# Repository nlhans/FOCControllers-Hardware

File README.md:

# FOCControllers
Exploring the world of FOC with BLDC/Steppers for custom haptic/force feedback in game controllers

Design is WIP.

## MCU
After some exploration, I've chosen to base this design around the STM32H725. There were several close runner ups, including some STM32G4 and F7 parts, and most honourable mention the RP2350. However, the RP2350 was not available from Mouser etc. at the time I started CAD. 
The secondary reason for the STM32H725 is that I still have a handful of these chips unassigned to a project in my parts bin. Considering they weren't cheap while coming in the "large brick" LQFP-176 package, this seemed like a good excuse to finally use them (-: 

Joking aside, this part is quite well suited for experiments with BLDC. Empirical observations using a Nucleo-H743 and the Arduino SimpleFOC library showed that the loopFOC() and move() functions take approximately 3.8 - 4.0us to execute on this chip (approx 1900 CPU cycles). This does not include sensor I/O. That means that running the FOC loop at 5-25kHz (depending on the position sensor datarate) will use around 2-10\% of CPU time. However, in this design I will be using this chip to drive 3 motors, which could bring up the CPU load to 30\%. 

This CPU time excludes I/O time from I2C/SPI bus transfers, or ADC data retrieval, "actual" FOC with DC current feedback, and more importantly, and force feedback algorithms. I would expect when this is all included that 25kHz loop speed would be quite the challenge.

I have also considered the RP2040, as I've used it for some exploration before concluding this design. However its lack of FPU and Cortex-M0+ could not do FOC loop calculations at more than 1kHz due to widespread floating point usage in SimpleFOC. Perhaps 2kHz was attainable when the slow I2C I/O is offloaded to the second core.. but 2kHz is still not a terrific loop speed. It didn't make sense to go through all that effort.

## Motor Driver
I have chosen to use the DRV8316C BLDC driver from Texas Instruments. This chip can use 6-PWM or 3-PWM mode with ENABLE input. The latter is necessary for SimpleFOC implementation of PWM and truth table to the (half-)H bridge drivers. Previous experiments with cheap DRV8833 boards were able to drive a BLDC motor, however, it was not controlling the DRV8833s properly due to its truth table orientated at brushed motor control (long story..). 

Moreover, the DRV8316C chip can operate with 24V supply. and drive 3-5A into motors. I plan to use this magnitude of power for developing an active pedal for simrig racing. These typically require motors in the order of 60-90Watt peak. 

The whole board will be fused for a continuous current of 5A. This may seem awkward to divide across 3 channels, but I expect the duty cycle and concurrent power output to be quite low for this application.

##  Sensing
The board contains, per motor channel, the interfaces for the following sensors:

- I2C magnetic encoders (e.g. As5600)
- SPI or Infineon SSC magnetic encoders (e.g. TLE5012B or TLI5012B)
- Lineair Potentiometer
- NTC for motor temperature
- Current Sense for all 3 coil outputs

The analog sensor channels are connected to a dedicated ADC on the STM32H7 each. The chip will be programmed to convert all channels on each FOC cycle.

All analog channels are referenced against a 3.0V voltage reference. BLDC channel 1 contains a 3.0V regulator to power the analog electronics for all 3 motor channels.

## Other stuff
The PCB contains several support functions which should aid for a configurable & robust driver:

- I2C 24AAxx EEPROM (bitbanged)
- I2C temperature sensor near driver of channel 2 (bitbanged)
- Voltage/Current monitor of input supply
- 5V/Vin 4-pin PWM fan with tacho readout. The board has a 80x80mm form factor in case it runs hot.
- Power clamp to dump regen power (if necessary).
- SPI interface for driving a small LCD
- I2C Grove Connector (hardware I2C)
- 2 UARTs
- 4 Debug LEDs
- 2 Push Buttons
- SWD debug

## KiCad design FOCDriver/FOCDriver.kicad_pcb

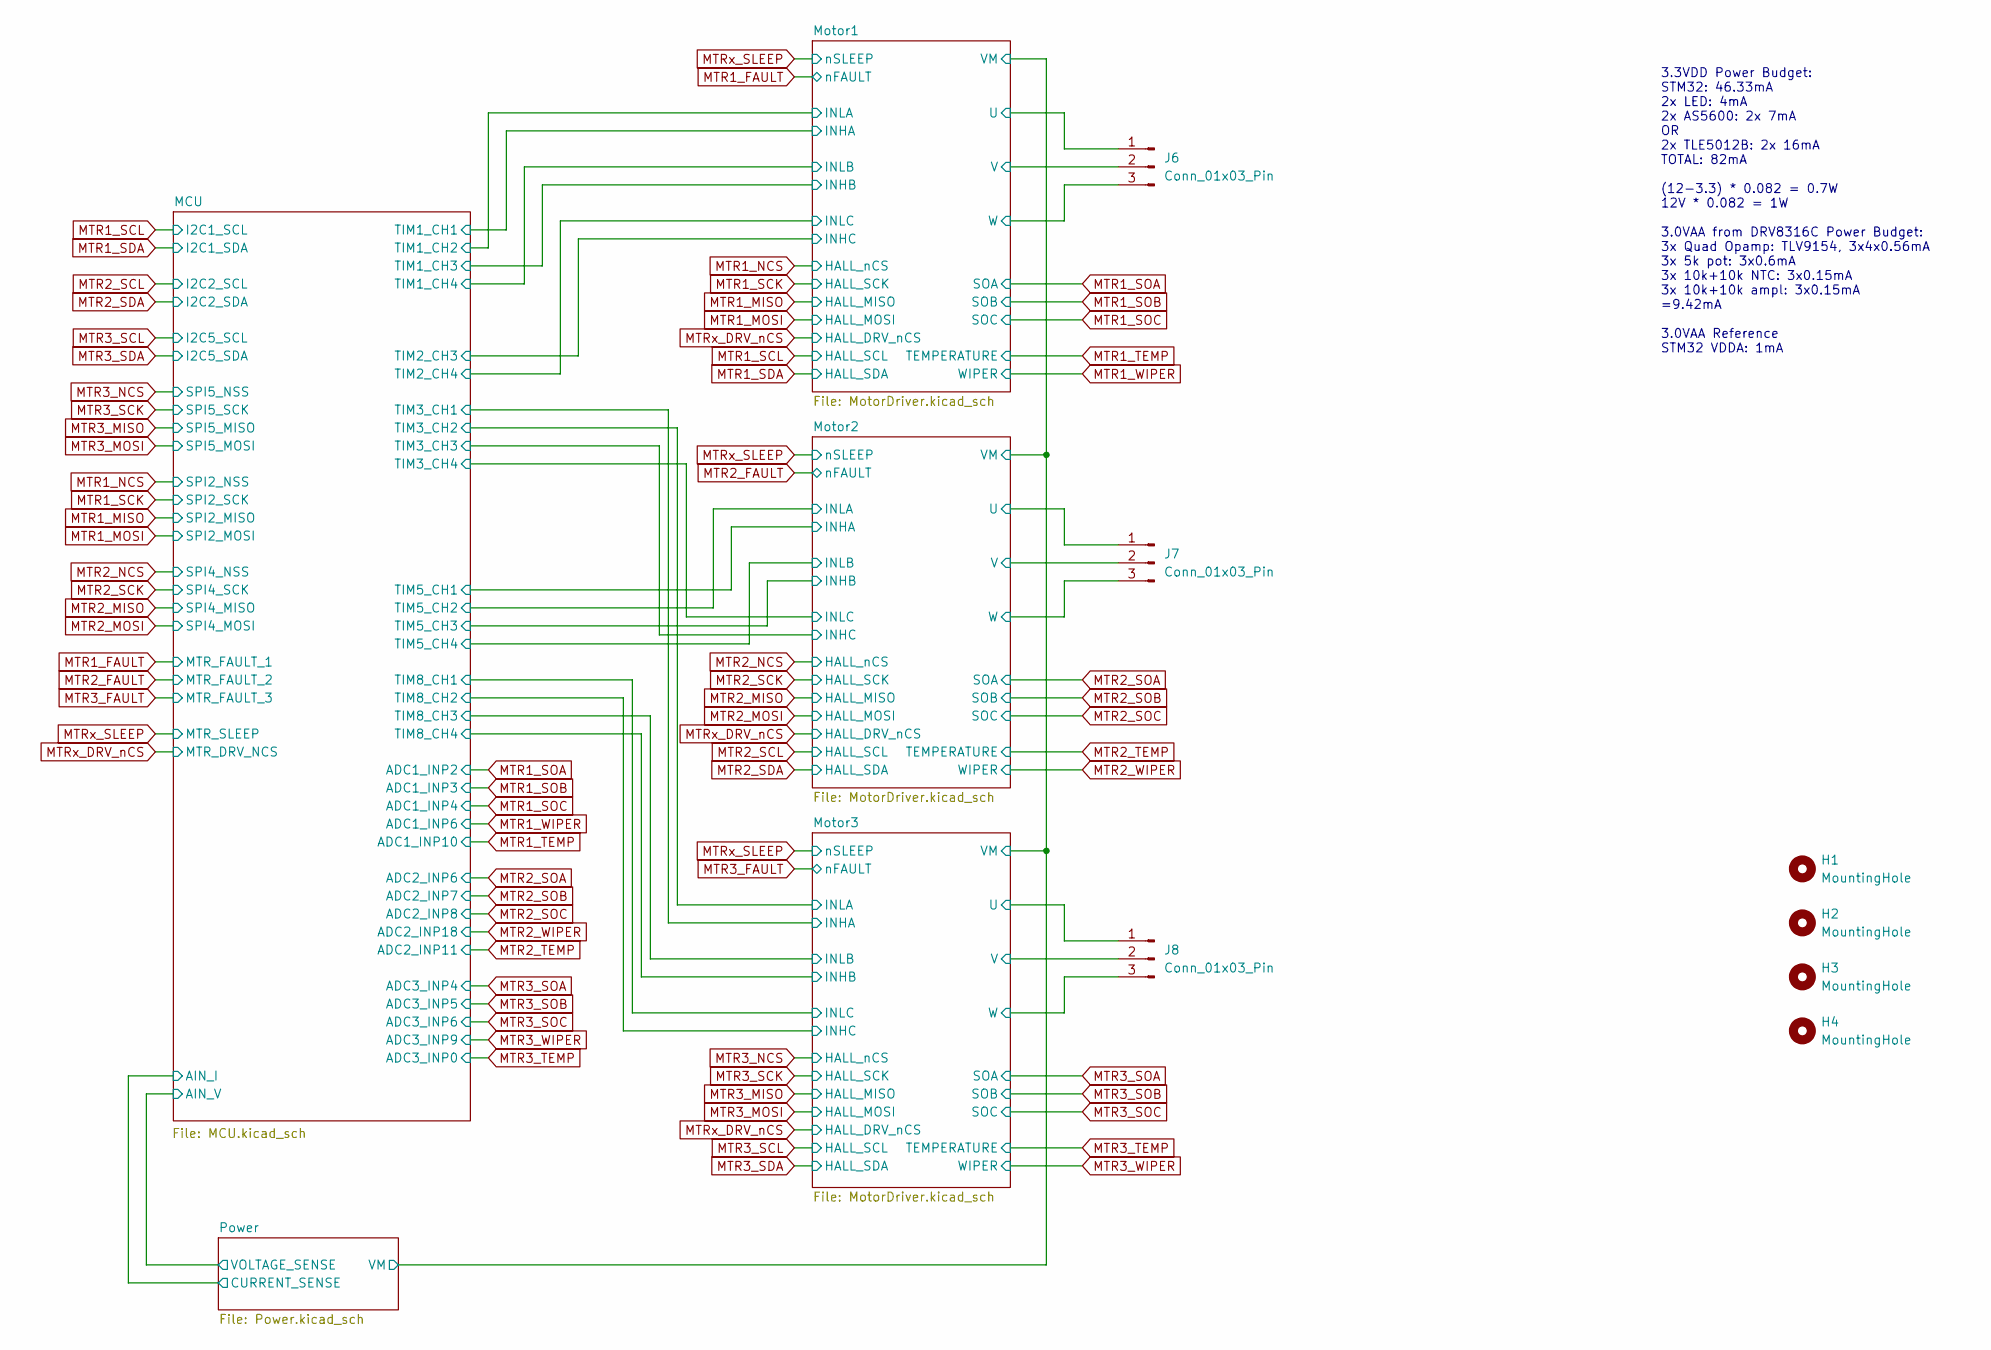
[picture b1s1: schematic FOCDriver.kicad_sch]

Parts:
H1, H2, H3, H4: MountingHole; MountingHole_3.2mm_M3
J6, J7, J8: Conn_01x03_Pin; PinSocket_1x03_P2.54mm_Vertical

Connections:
/Motor1/U: J6.1; also elsewhere on the board
/Motor1/V: J6.2; also elsewhere on the board
/Motor1/W: J6.3; also elsewhere on the board
/Motor2/U: J7.1; also elsewhere on the board
/Motor2/V: J7.2; also elsewhere on the board
/Motor2/W: J7.3; also elsewhere on the board
/Motor3/U: J8.1; also elsewhere on the board
/Motor3/V: J8.2; also elsewhere on the board
/Motor3/W: J8.3; also elsewhere on the board

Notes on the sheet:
3.3VDD Power Budget: STM32: 46.33mA 2x LED: 4mA 2x AS5600: 2x 7mA OR 2x TLE5012B: 2x 16mA TOTAL: 82mA (12-3.3) * 0.082 = 0.7W 12V * 0.082 = 1W 3.0VAA from DRV8316C Power Budget: 3x Quad Opamp: TLV9154, 3x4x0.56mA 3x 5k pot: 3x0.6mA 3x 10k+10k NTC: 3x0.15mA 3x 10k+10k ampl: 3x0.15mA =9.42mA 3.0VAA R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

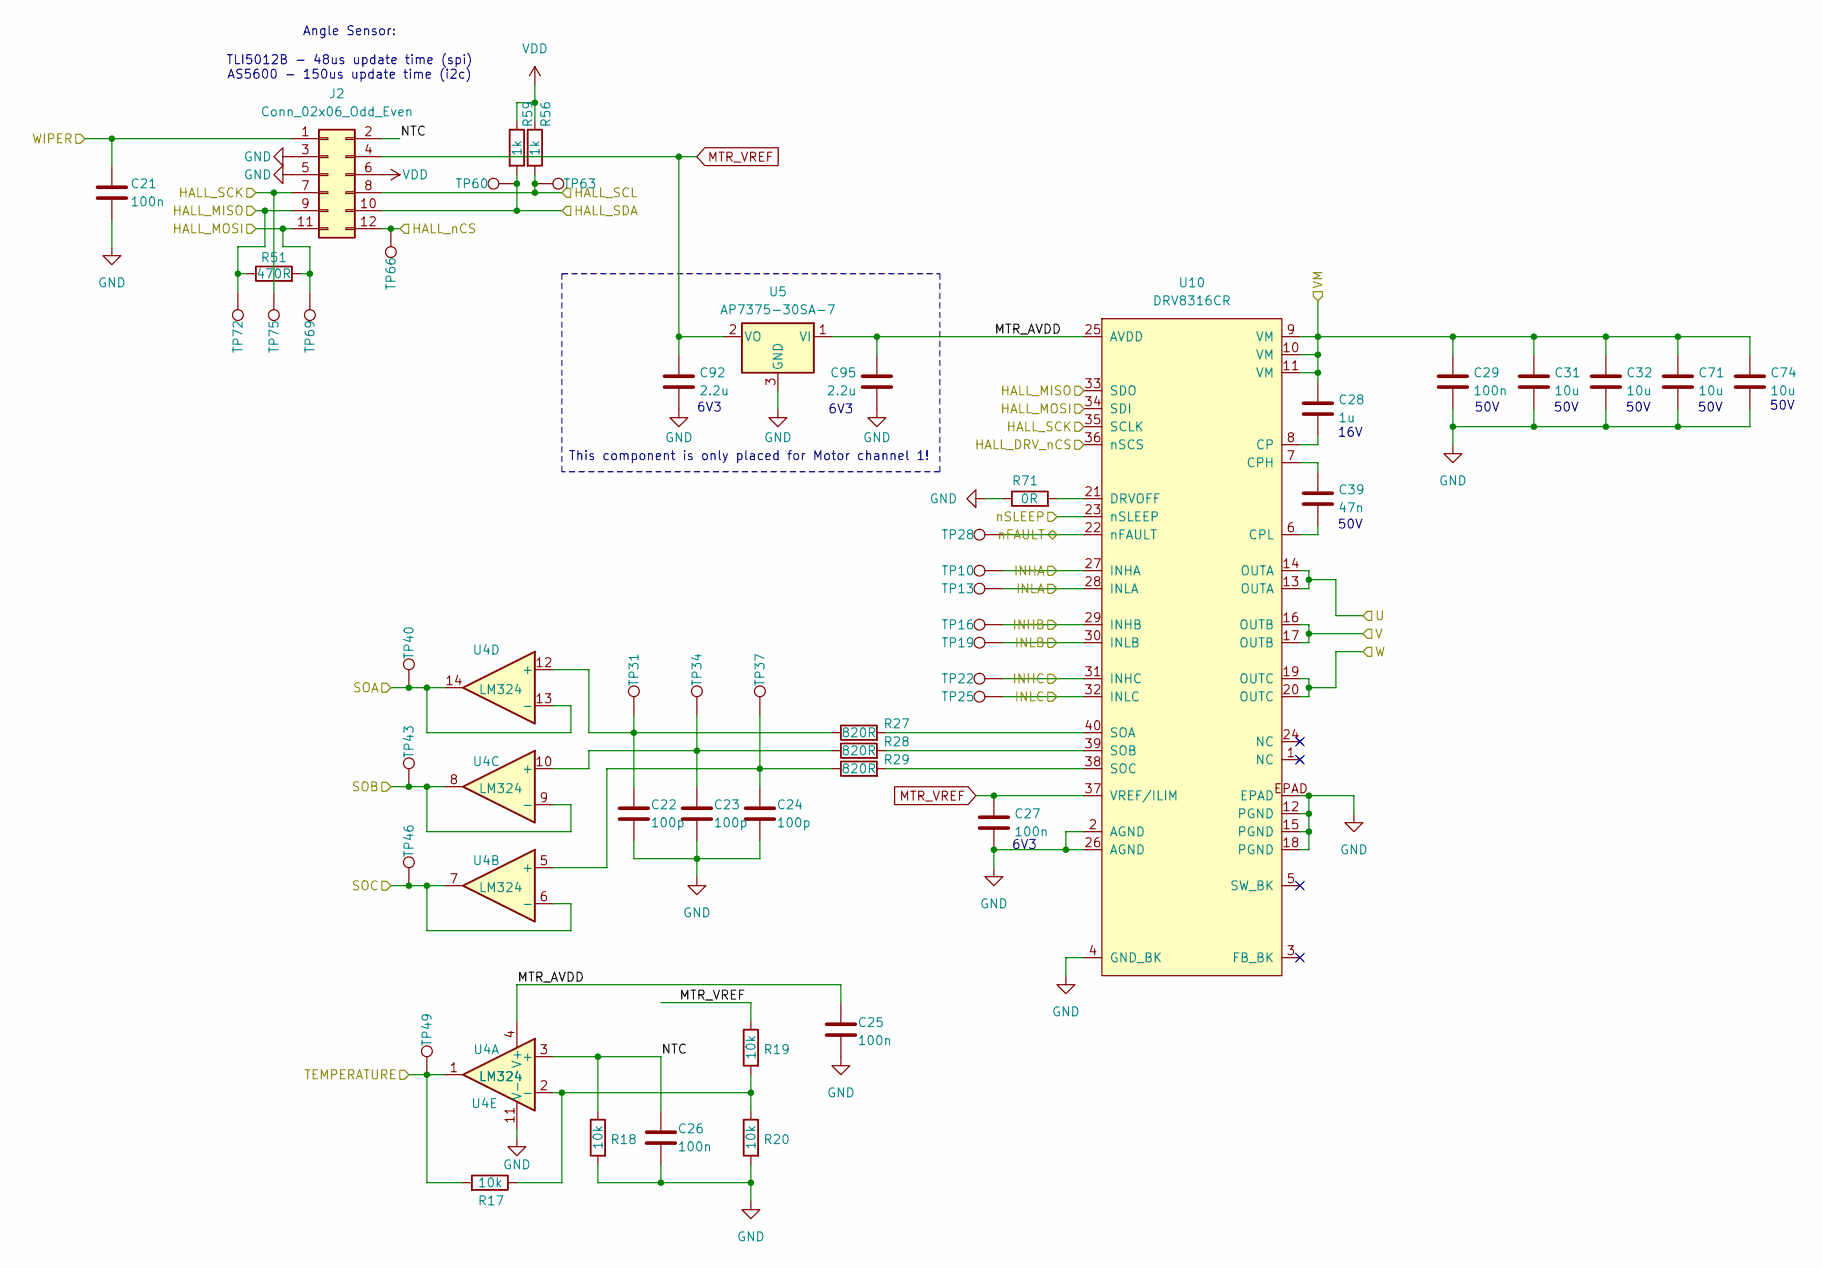
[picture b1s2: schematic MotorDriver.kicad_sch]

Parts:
C21, C25, C26, C27: 100n; Nice_0402C
C22, C23, C24: 100p; Nice_0402C
C28: 1u; Nice_0603C
C29: 100n; Nice_0603C
C31, C32, C71, C74: 10u; C_1206_3216Metric
C39: 47n; Nice_0603C
C92, C95: 2.2u; Nice_0603C
J2: Conn_02x06_Odd_Even; PinSocket_2x06_P2.54mm_Horizontal
R17, R18, R19, R20: 10k; Nice_0402R
R27, R28, R29: 820R; Nice_0402R
R51: 470R; Nice_0402R
R56, R59: 1k; Nice_0402R
R71: 0R; Nice_0402R
TP10, TP13, TP16, TP19, TP22, TP25, TP28, TP31, TP34, TP37, TP40, TP43, TP46, TP49, TP60, TP63, TP66, TP69, TP72, TP75: TestPoint; TP_0.6mm
U4: LM324; TSSOP-14_4.4x5mm_P0.65mm
U5: AP7375-30SA-7; SOT-23; MPN AP7375-30SA-7
U10: DRV8316CR; VQFN40_RGF_TEX; MPN DRV8316CRRGFR

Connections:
/MCU/TIM1_CH1: TP10.1, U10.27 (INHA); also elsewhere on the board
/MCU/TIM1_CH2: TP13.1, U10.28 (INLA); also elsewhere on the board
/MCU/TIM1_CH3: TP16.1, U10.29 (INHB); also elsewhere on the board
/MCU/TIM1_CH4: TP19.1, U10.30 (INLB); also elsewhere on the board
/MCU/TIM2_CH3: TP22.1, U10.31 (INHC); also elsewhere on the board
/MCU/TIM2_CH4: TP25.1, U10.32 (INLC); also elsewhere on the board
/Motor1/MTR_AVDD: C25.1, C95.1, U4.4 (V+), U5.1 (VI), U10.25 (AVDD)
/Motor1/NTC: C26.1, J2.2, R18.1, U4.3 (+)
/Motor1/U: U10.13 (OUTA), U10.14 (OUTA); also elsewhere on the board
/Motor1/V: U10.16 (OUTB), U10.17 (OUTB); also elsewhere on the board
/Motor1/VM: C28.1, C29.1, C31.1, C32.1, C71.1, C74.1, U10.9 (VM), U10.10 (VM), U10.11 (VM); also elsewhere on the board
/Motor1/W: U10.19 (OUTC), U10.20 (OUTC); also elsewhere on the board
GND: C21.2, C22.2, C23.2, C24.2, C25.2, C26.2, C27.2, C29.2, C31.2, C32.2, C71.2, C74.2, C92.2, C95.2, J2.3, J2.5, R18.2, R20.2, R71.1, U4.11 (V-), U5.3 (GND), U10.2 (AGND), U10.4 (GND_BK), U10.12 (PGND), U10.15 (PGND), U10.18 (PGND), U10.26 (AGND), U10.EPAD; also elsewhere on the board
MTR1_FAULT: TP28.1, U10.22 (nFAULT); also elsewhere on the board
MTR1_MISO: J2.9, R51.1, TP72.1, U10.33 (SDO); also elsewhere on the board
MTR1_MOSI: J2.11, R51.2, TP69.1, U10.34 (SDI); also elsewhere on the board
MTR1_NCS: J2.12, TP66.1; also elsewhere on the board
MTR1_SCK: J2.7, TP75.1, U10.35 (SCLK); also elsewhere on the board
MTR1_SCL: J2.8, R56.2, TP63.1; also elsewhere on the board
MTR1_SDA: J2.10, R59.2, TP60.1; also elsewhere on the board
MTR1_SOA: TP40.1, U4.13 (-), U4.14; also elsewhere on the board
MTR1_SOB: TP43.1, U4.8, U4.9 (-); also elsewhere on the board
MTR1_SOC: TP46.1, U4.6 (-), U4.7; also elsewhere on the board
MTR1_TEMP: R17.2, TP49.1, U4.1; also elsewhere on the board
MTR1_WIPER: C21.1, J2.1; also elsewhere on the board
MTR_VREF: C27.1, C92.1, J2.4, R19.1, U5.2 (VO), U10.37 (VREF/ILIM); also elsewhere on the board
MTRx_DRV_nCS: U10.36 (nSCS); also elsewhere on the board
MTRx_SLEEP: U10.23 (nSLEEP); also elsewhere on the board
unnamed: R17.1, R19.2, R20.1, U4.2 (-)
unnamed: C24.1, R29.1, TP37.1, U4.5 (+)
unnamed: C23.1, R28.1, TP34.1, U4.10 (+)
unnamed: C22.1, R27.1, TP31.1, U4.12 (+)
unnamed: C28.2, U10.8 (CP)
unnamed: C39.1, U10.7 (CPH)
unnamed: C39.2, U10.6 (CPL)
unnamed: R71.2, U10.21 (DRVOFF)
unnamed: R27.2, U10.40 (SOA)
unnamed: R28.2, U10.39 (SOB)
unnamed: R29.2, U10.38 (SOC)
VDD: J2.6, R56.1, R59.1; also elsewhere on the board

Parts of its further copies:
C9, C13, C15, C34, C38, C40, C88, C89: 100n; Nice_0402C
C10, C11, C12, C35, C36, C37: 100p; Nice_0402C
C16, C41: 1u; Nice_0603C
C17, C42: 100n; Nice_0603C
C19, C20, C44, C45, C72, C73, C75, C76: 10u; C_1206_3216Metric
C48, C87: 47n; Nice_0603C
C96, C97: 2.2u; Nice_0603C
J1, J3: Conn_02x06_Odd_Even; PinSocket_2x06_P2.54mm_Horizontal
R4, R5, R6, R7, R33, R34, R35, R36: 10k; Nice_0402R
R14, R15, R16, R43, R44, R45: 820R; Nice_0402R
R52, R65: 470R; Nice_0402R
R57, R58, R60, R61: 1k; Nice_0402R
R72, R73: 0R; Nice_0402R
TP11, TP12, TP14, TP15, TP17, TP18, TP20, TP21, TP23, TP24, TP26, TP27, TP29, TP30, TP32, TP33, TP35, TP36, TP38, TP39, TP41, TP42, TP44, TP45, TP47, TP48, TP50, TP51, TP61, TP62, TP64, TP65, TP67, TP68, TP70, TP71, TP73, TP74, TP76, TP77: TestPoint; TP_0.6mm
U2, U7: LM324; TSSOP-14_4.4x5mm_P0.65mm
U15, U16: DRV8316CR; VQFN40_RGF_TEX; MPN DRV8316CRRGFR

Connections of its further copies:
/MCU/TIM3_CH1: TP12.1, U16.27 (INHA); also elsewhere on the board
/MCU/TIM3_CH2: TP15.1, U16.28 (INLA); also elsewhere on the board
/MCU/TIM3_CH3: TP23.1, U15.31 (INHC); also elsewhere on the board
/MCU/TIM3_CH4: TP26.1, U15.32 (INLC); also elsewhere on the board
/MCU/TIM5_CH1: TP11.1, U15.27 (INHA); also elsewhere on the board
/MCU/TIM5_CH2: TP14.1, U15.28 (INLA); also elsewhere on the board
/MCU/TIM5_CH3: TP17.1, U15.29 (INHB); also elsewhere on the board
/MCU/TIM5_CH4: TP20.1, U15.30 (INLB); also elsewhere on the board
/MCU/TIM8_CH1: TP27.1, U16.32 (INLC); also elsewhere on the board
/MCU/TIM8_CH2: TP24.1, U16.31 (INHC); also elsewhere on the board
/MCU/TIM8_CH3: TP21.1, U16.30 (INLB); also elsewhere on the board
/MCU/TIM8_CH4: TP18.1, U16.29 (INHB); also elsewhere on the board
/Motor1/VM: C16.1, C17.1, C19.1, C20.1, C41.1, C42.1, C44.1, C45.1, C72.1, C73.1, C75.1, C76.1, U15.9 (VM), U15.10 (VM), U15.11 (VM), U16.9 (VM), U16.10 (VM), U16.11 (VM); also elsewhere on the board
/Motor2/MTR_AVDD: C13.1, C96.1, U2.4 (V+), U15.25 (AVDD)
/Motor2/NTC: C88.1, J1.2, R5.1, U2.3 (+)
/Motor2/U: U15.13 (OUTA), U15.14 (OUTA); also elsewhere on the board
/Motor2/V: U15.16 (OUTB), U15.17 (OUTB); also elsewhere on the board
/Motor2/W: U15.19 (OUTC), U15.20 (OUTC); also elsewhere on the board
/Motor3/MTR_AVDD: C38.1, C97.1, U7.4 (V+), U16.25 (AVDD)
/Motor3/NTC: C89.1, J3.2, R34.1, U7.3 (+)
/Motor3/U: U16.13 (OUTA), U16.14 (OUTA); also elsewhere on the board
/Motor3/V: U16.16 (OUTB), U16.17 (OUTB); also elsewhere on the board
/Motor3/W: U16.19 (OUTC), U16.20 (OUTC); also elsewhere on the board
GND: C9.2, C10.2, C11.2, C12.2, C13.2, C15.2, C17.2, C19.2, C20.2, C34.2, C35.2, C36.2, C37.2, C38.2, C40.2, C42.2, C44.2, C45.2, C72.2, C73.2, C75.2, C76.2, C88.2, C89.2, C96.2, C97.2, J1.3, J1.5, J3.3, J3.5, R5.2, R7.2, R34.2, R36.2, R72.1, R73.1, U2.11 (V-), U7.11 (V-), U15.2 (AGND), U15.4 (GND_BK), U15.12 (PGND), U15.15 (PGND), U15.18 (PGND), U15.26 (AGND), U15.EPAD, U16.2 (AGND), U16.4 (GND_BK), U16.12 (PGND), U16.15 (PGND), U16.18 (PGND), U16.26 (AGND), U16.EPAD; also elsewhere on the board
MTR2_FAULT: TP29.1, U15.22 (nFAULT); also elsewhere on the board
MTR2_MISO: J1.9, R52.1, TP73.1, U15.33 (SDO); also elsewhere on the board
MTR2_MOSI: J1.11, R52.2, TP70.1, U15.34 (SDI); also elsewhere on the board
MTR2_NCS: J1.12, TP67.1; also elsewhere on the board
MTR2_SCK: J1.7, TP76.1, U15.35 (SCLK); also elsewhere on the board
MTR2_SCL: J1.8, R57.2, TP64.1; also elsewhere on the board
MTR2_SDA: J1.10, R60.2, TP61.1; also elsewhere on the board
MTR2_SOA: TP41.1, U2.13 (-), U2.14; also elsewhere on the board
MTR2_SOB: TP44.1, U2.8, U2.9 (-); also elsewhere on the board
MTR2_SOC: TP47.1, U2.6 (-), U2.7; also elsewhere on the board
MTR2_TEMP: R4.2, TP50.1, U2.1; also elsewhere on the board
MTR2_WIPER: C9.1, J1.1; also elsewhere on the board
MTR3_FAULT: TP30.1, U16.22 (nFAULT); also elsewhere on the board
MTR3_MISO: J3.9, R65.1, TP74.1, U16.33 (SDO); also elsewhere on the board
MTR3_MOSI: J3.11, R65.2, TP71.1, U16.34 (SDI); also elsewhere on the board
MTR3_NCS: J3.12, TP68.1; also elsewhere on the board
MTR3_SCK: J3.7, TP77.1, U16.35 (SCLK); also elsewhere on the board
MTR3_SCL: J3.8, R58.2, TP65.1; also elsewhere on the board
MTR3_SDA: J3.10, R61.2, TP62.1; also elsewhere on the board
MTR3_SOA: TP42.1, U7.13 (-), U7.14; also elsewhere on the board
MTR3_SOB: TP45.1, U7.8, U7.9 (-); also elsewhere on the board
MTR3_SOC: TP48.1, U7.6 (-), U7.7; also elsewhere on the board
MTR3_TEMP: R33.2, TP51.1, U7.1; also elsewhere on the board
MTR3_WIPER: C34.1, J3.1; also elsewhere on the board
MTR_VREF: C15.1, C40.1, J1.4, J3.4, R6.1, R35.1, U15.37 (VREF/ILIM), U16.37 (VREF/ILIM); also elsewhere on the board
MTRx_DRV_nCS: U15.36 (nSCS), U16.36 (nSCS); also elsewhere on the board
MTRx_SLEEP: U15.23 (nSLEEP), U16.23 (nSLEEP); also elsewhere on the board
unnamed: R4.1, R6.2, R7.1, U2.2 (-)
unnamed: C12.1, R16.1, TP38.1, U2.5 (+)
unnamed: C11.1, R15.1, TP35.1, U2.10 (+)
unnamed: C10.1, R14.1, TP32.1, U2.12 (+)
unnamed: R33.1, R35.2, R36.1, U7.2 (-)
unnamed: C37.1, R45.1, TP39.1, U7.5 (+)
unnamed: C36.1, R44.1, TP36.1, U7.10 (+)
unnamed: C35.1, R43.1, TP33.1, U7.12 (+)
unnamed: C16.2, U15.8 (CP)
unnamed: C48.1, U15.7 (CPH)
unnamed: C48.2, U15.6 (CPL)
unnamed: R72.2, U15.21 (DRVOFF)
unnamed: R14.2, U15.40 (SOA)
unnamed: R15.2, U15.39 (SOB)
unnamed: R16.2, U15.38 (SOC)
unnamed: C41.2, U16.8 (CP)
unnamed: C87.1, U16.7 (CPH)
unnamed: C87.2, U16.6 (CPL)
unnamed: R73.2, U16.21 (DRVOFF)
unnamed: R43.2, U16.40 (SOA)
unnamed: R44.2, U16.39 (SOB)
unnamed: R45.2, U16.38 (SOC)
VDD: J1.6, J3.6, R57.1, R58.1, R60.1, R61.1; also elsewhere on the board

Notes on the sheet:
50V
Angle Sensor: TLI5012B - 48us update time (spi) AS5600 - 150us update time (i2c)
6V3
16V
This component is only placed for Motor channel 1!

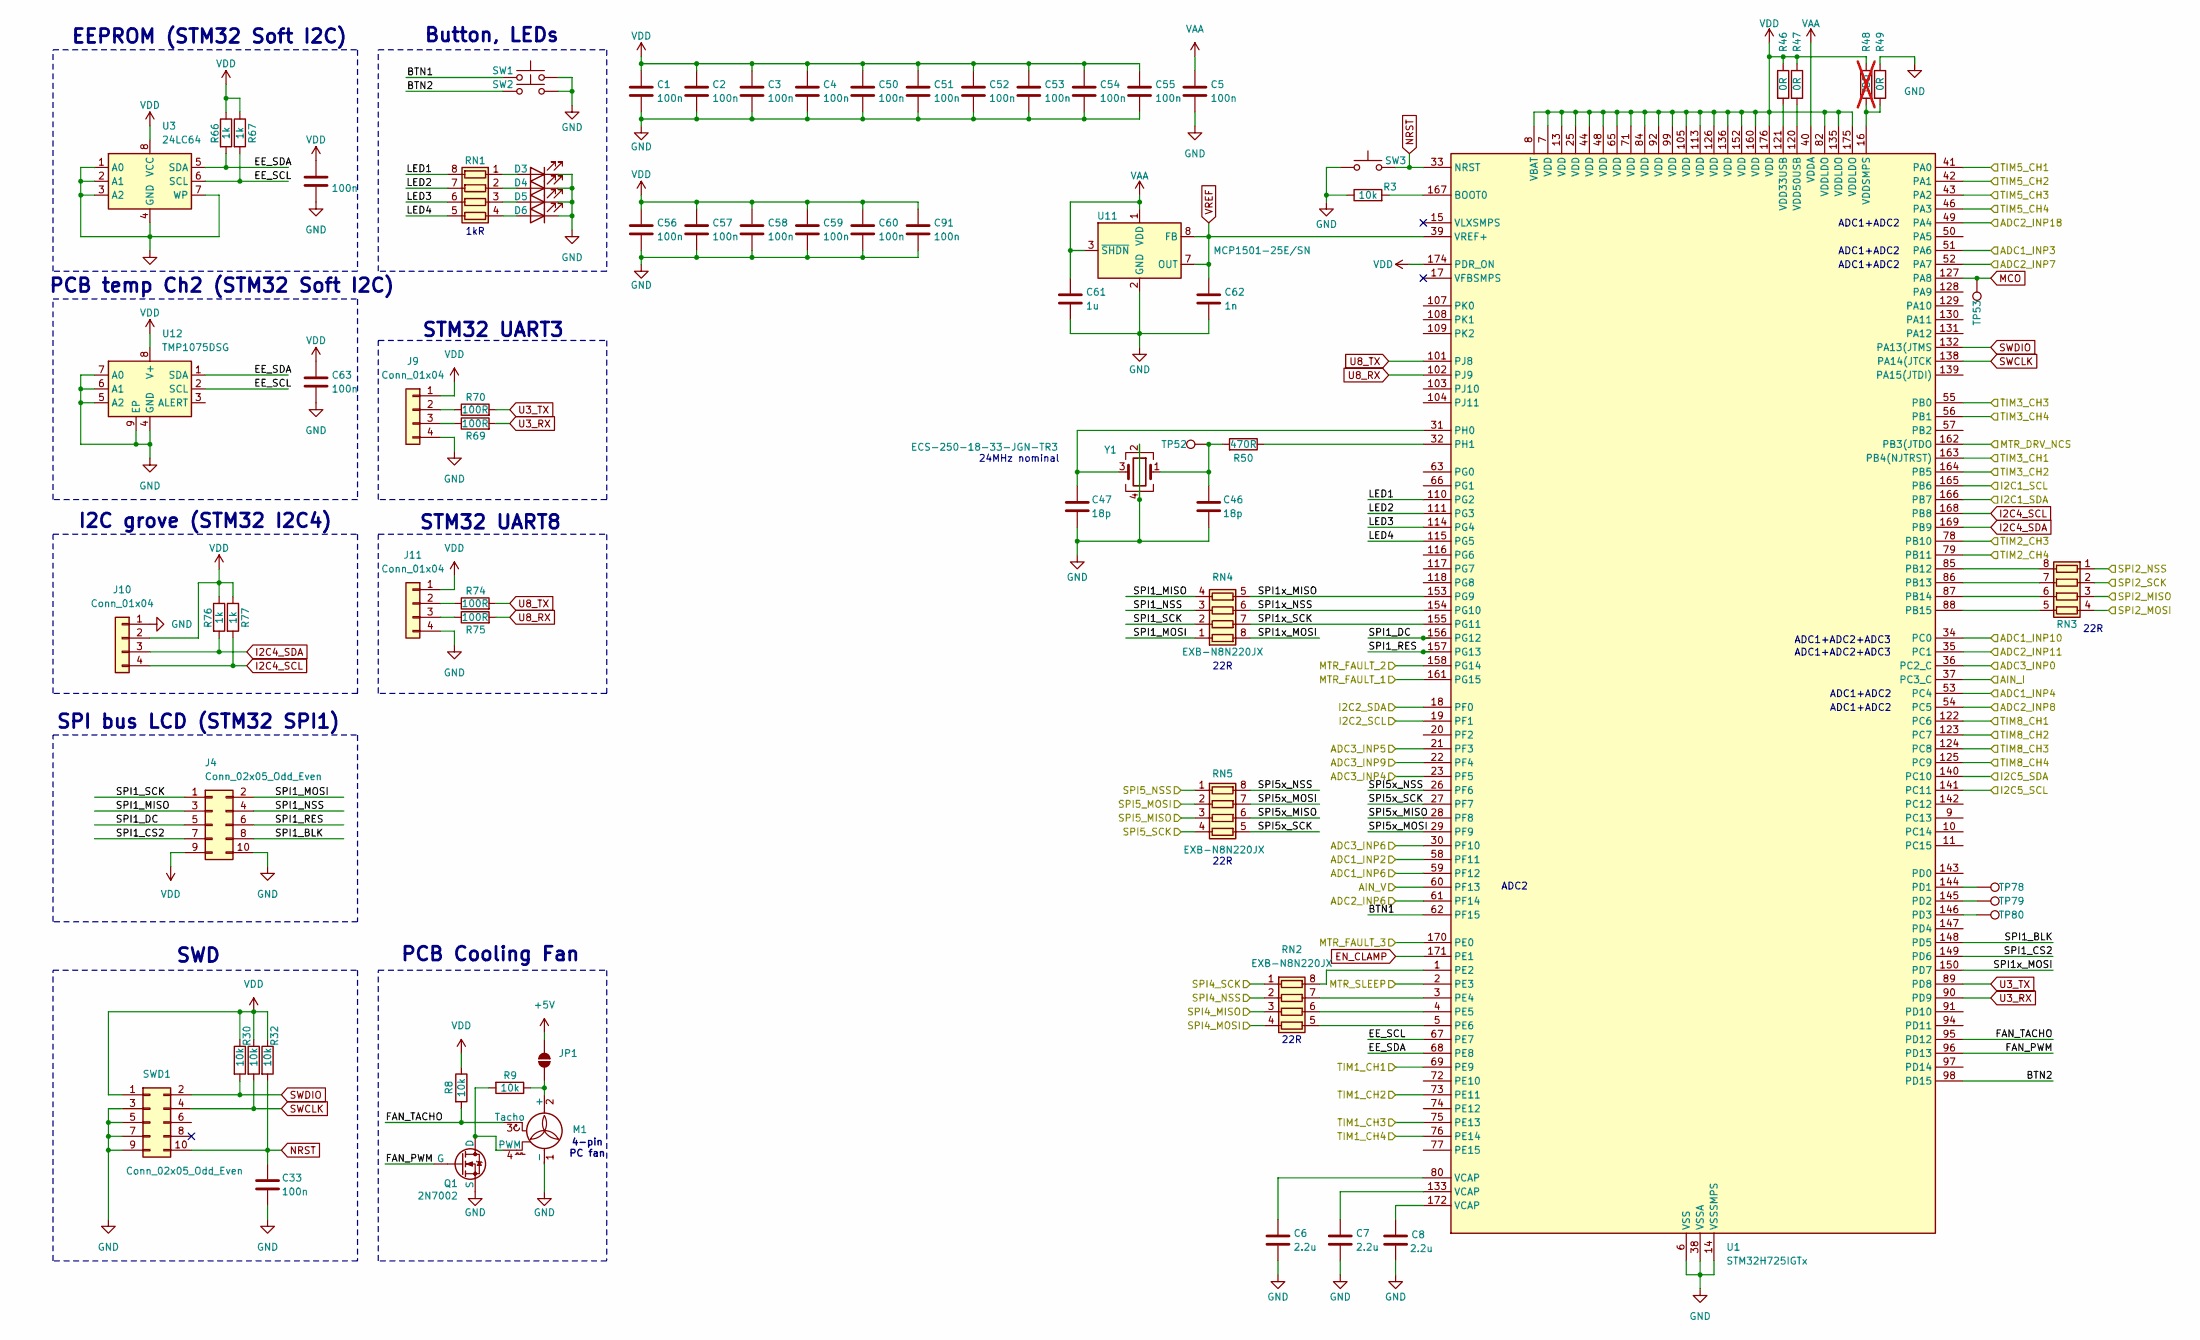
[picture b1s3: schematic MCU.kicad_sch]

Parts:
C1, C2, C3, C4, C5, C33, C49, C50, C51, C52, C53, C54, C55, C56, C57, C58, C59, C60, C63, C91: 100n; Nice_0402C
C6, C7, C8: 2.2u; Nice_0603C
C46, C47: 18p; Nice_0402C
C61: 1u; Nice_0603C
C62: 1n; Nice_0402C
D3, D4, D5, D6: APT2012SYCK; LED_0805_2012Metric; MPN APT2012SYCK
J4: Conn_02x05_Odd_Even; PinHeader_2x05_P2.54mm_Vertical
J9, J11: Conn_01x04; PinHeader_1x04_P2.54mm_Vertical
J10: Conn_01x04; JST_PH_B4B-PH-K_1x04_P2.00mm_Vertical
JP1: SolderJumper_2_Open; SolderJumper-2_P1.3mm_Open_Pad1.0x1.5mm
M1: Fan_Tacho_PWM; FanPinHeader_1x04_P2.54mm_Vertical
Q1: 2N7002; SOT-23
R3, R8, R9, R30, R31, R32: 10k; Nice_0402R
R46, R47, R49: 0R; Nice_0402R
R48: TBD; Nice_0402DNP; not fitted
R50: 470R; Nice_0402R
R66, R67, R76, R77: 1k; Nice_0402R
R69, R70, R74, R75: 100R; Nice_0402R
RN1: EXB-38V102JV; R_Array_Convex_4x0603
RN2, RN3, RN4, RN5: EXB-N8N220JX; R_Array_Concave_4x0402
SW1, SW2, SW3: SW_Push; SW_PUSH_1P1T_6x3.5mm_H5.0_APEM_MJTP1250
SWD1: Conn_02x05_Odd_Even; PinHeader_2x05_P1.27mm_Vertical_SMD
TP52, TP53, TP78, TP79, TP80: TestPoint; TP_0.6mm
U1: STM32H725IGTx; LQFP-176_24x24mm_P0.5mm
U3: 24LC64; SOIC-8_3.9x4.9mm_P1.27mm
U11: MCP1501-25E/SN; SOIC-8_3.9x4.9mm_P1.27mm; MPN MCP1501-25E/SN
U12: TMP1075DSG; WSON-8-1EP_2x2mm_P0.5mm_EP0.9x1.6mm_ThermalVias
Y1: ECS-250-18-33-JGN-TR3; Crystal_SMD_3225-4Pin_3.2x2.5mm; MPN ECS-250-18-33-JGN-TR3

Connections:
+5V: JP1.2 (B); also elsewhere on the board
/MCU/AIN_I: U1.37 (PC3_C); also elsewhere on the board
/MCU/AIN_V: U1.60 (PF13); also elsewhere on the board
/MCU/BTN1: SW1.2, U1.62 (PF15)
/MCU/BTN2: SW2.2, U1.98 (PD15)
/MCU/EE_SCL: R67.2, U1.67 (PE7), U3.6 (SCL), U12.2 (SCL)
/MCU/EE_SDA: R66.2, U1.68 (PE8), U3.5 (SDA), U12.1 (SDA)
/MCU/FAN_PWM: Q1.1 (G), U1.96 (PD13)
/MCU/FAN_TACHO: M1.3 (Tacho), R8.2, U1.95 (PD12)
/MCU/LED1: RN1.8 (R1.2), U1.110 (PG2)
/MCU/LED2: RN1.7 (R2.2), U1.111 (PG3)
/MCU/LED3: RN1.6 (R3.2), U1.114 (PG4)
/MCU/LED4: RN1.5 (R4.2), U1.115 (PG5)
/MCU/SPI1_BLK: J4.8, U1.148 (PD5)
/MCU/SPI1_CS2: J4.7, U1.149 (PD6)
/MCU/SPI1_DC: J4.5, U1.156 (PG12)
/MCU/SPI1_MISO: J4.3, RN4.4 (R4.1)
/MCU/SPI1_MOSI: J4.2, RN4.1 (R1.1)
/MCU/SPI1_NSS: J4.4, RN4.3 (R3.1)
/MCU/SPI1_RES: J4.6, U1.157 (PG13)
/MCU/SPI1_SCK: J4.1, RN4.2 (R2.1)
/MCU/SPI1x_MISO: RN4.5 (R4.2), U1.153 (PG9)
/MCU/SPI1x_MOSI: RN4.8 (R1.2), U1.150 (PD7)
/MCU/SPI1x_NSS: RN4.6 (R3.2), U1.154 (PG10)
/MCU/SPI1x_SCK: RN4.7 (R2.2), U1.155 (PG11)
/MCU/SPI5x_MISO: RN5.6 (R3.2), U1.28 (PF8)
/MCU/SPI5x_MOSI: RN5.7 (R2.2), U1.29 (PF9)
/MCU/SPI5x_NSS: RN5.8 (R1.2), U1.26 (PF6)
/MCU/SPI5x_SCK: RN5.5 (R4.2), U1.27 (PF7)
/MCU/TIM1_CH1: U1.69 (PE9); also elsewhere on the board
/MCU/TIM1_CH2: U1.73 (PE11); also elsewhere on the board
/MCU/TIM1_CH3: U1.75 (PE13); also elsewhere on the board
/MCU/TIM1_CH4: U1.76 (PE14); also elsewhere on the board
/MCU/TIM2_CH3: U1.78 (PB10); also elsewhere on the board
/MCU/TIM2_CH4: U1.79 (PB11); also elsewhere on the board
/MCU/TIM3_CH1: U1.163 (PB4(NJTRST)); also elsewhere on the board
/MCU/TIM3_CH2: U1.164 (PB5); also elsewhere on the board
/MCU/TIM3_CH3: U1.55 (PB0); also elsewhere on the board
/MCU/TIM3_CH4: U1.56 (PB1); also elsewhere on the board
/MCU/TIM5_CH1: U1.41 (PA0); also elsewhere on the board
/MCU/TIM5_CH2: U1.42 (PA1); also elsewhere on the board
/MCU/TIM5_CH3: U1.43 (PA2); also elsewhere on the board
/MCU/TIM5_CH4: U1.46 (PA3); also elsewhere on the board
/MCU/TIM8_CH1: U1.122 (PC6); also elsewhere on the board
/MCU/TIM8_CH2: U1.123 (PC7); also elsewhere on the board
/MCU/TIM8_CH3: U1.124 (PC8); also elsewhere on the board
/MCU/TIM8_CH4: U1.125 (PC9); also elsewhere on the board
EN_CLAMP: U1.171 (PE1); also elsewhere on the board
GND: C1.2, C2.2, C3.2, C4.2, C5.2, C6.2, C7.2, C8.2, C33.2, C46.2, C47.2, C49.2, C50.2, C51.2, C52.2, C53.2, C54.2, C55.2, C56.2, C57.2, C58.2, C59.2, C60.2, C61.2, C62.2, C63.2, C91.2, D3.1 (K), D4.1 (K), D5.1 (K), D6.1 (K), J4.10, J9.4, J10.1, J11.4, M1.1 (-), Q1.2 (S), R3.1, R49.1, SW1.1, SW2.1, SW3.1, SWD1.3, SWD1.5, SWD1.7, SWD1.9, U1.6 (VSS), U1.12 (VSS), U1.14 (VSSSMPS), U1.24 (VSS), U1.38 (VSSA), U1.45 (VSS), U1.47 (VSS), U1.64 (VSS), U1.70 (VSS), U1.81 (VSS), U1.83 (VSS), U1.93 (VSS), U1.100 (VSS), U1.106 (VSS), U1.112 (VSS), U1.119 (VSS), U1.134 (VSS), U1.137 (VSS), U1.151 (VSS), U1.159 (VSS), U1.173 (VSS), U3.1 (A0), U3.2 (A1), U3.3 (A2), U3.4 (GND), U3.7 (WP), U11.2 (GND), U11.4 (GND), U11.5 (GND), U11.6 (GND), U12.4 (GND), U12.5 (A2), U12.6 (A1), U12.7 (A0), U12.9 (EP), Y1.2, Y1.4; also elsewhere on the board
I2C4_SCL: J10.4, R77.2, U1.168 (PB8)
I2C4_SDA: J10.3, R76.2, U1.169 (PB9)
MCO: TP53.1, U1.127 (PA8)
MTR1_FAULT: U1.161 (PG15); also elsewhere on the board
MTR1_MISO: RN3.3 (R3.1); also elsewhere on the board
MTR1_MOSI: RN3.4 (R4.1); also elsewhere on the board
MTR1_NCS: RN3.1 (R1.1); also elsewhere on the board
MTR1_SCK: RN3.2 (R2.1); also elsewhere on the board
MTR1_SCL: U1.165 (PB6); also elsewhere on the board
MTR1_SDA: U1.166 (PB7); also elsewhere on the board
MTR1_SOA: U1.58 (PF11); also elsewhere on the board
MTR1_SOB: U1.51 (PA6); also elsewhere on the board
MTR1_SOC: U1.53 (PC4); also elsewhere on the board
MTR1_TEMP: U1.34 (PC0); also elsewhere on the board
MTR1_WIPER: U1.59 (PF12); also elsewhere on the board
MTR2_FAULT: U1.158 (PG14); also elsewhere on the board
MTR2_MISO: RN2.3 (R3.1); also elsewhere on the board
MTR2_MOSI: RN2.4 (R4.1); also elsewhere on the board
MTR2_NCS: RN2.2 (R2.1); also elsewhere on the board
MTR2_SCK: RN2.1 (R1.1); also elsewhere on the board
MTR2_SCL: U1.19 (PF1); also elsewhere on the board
MTR2_SDA: U1.18 (PF0); also elsewhere on the board
MTR2_SOA: U1.61 (PF14); also elsewhere on the board
MTR2_SOB: U1.52 (PA7); also elsewhere on the board
MTR2_SOC: U1.54 (PC5); also elsewhere on the board
MTR2_TEMP: U1.35 (PC1); also elsewhere on the board
MTR2_WIPER: U1.49 (PA4); also elsewhere on the board
MTR3_FAULT: U1.170 (PE0); also elsewhere on the board
MTR3_MISO: RN5.3 (R3.1); also elsewhere on the board
MTR3_MOSI: RN5.2 (R2.1); also elsewhere on the board
MTR3_NCS: RN5.1 (R1.1); also elsewhere on the board
MTR3_SCK: RN5.4 (R4.1); also elsewhere on the board
MTR3_SCL: U1.141 (PC11); also elsewhere on the board
MTR3_SDA: U1.140 (PC10); also elsewhere on the board
MTR3_SOA: U1.23 (PF5); also elsewhere on the board
MTR3_SOB: U1.21 (PF3); also elsewhere on the board
MTR3_SOC: U1.30 (PF10); also elsewhere on the board
MTR3_TEMP: U1.36 (PC2_C); also elsewhere on the board
MTR3_WIPER: U1.22 (PF4); also elsewhere on the board
MTRx_DRV_nCS: U1.162 (PB3(JTDO); also elsewhere on the board
MTRx_SLEEP: U1.2 (PE3); also elsewhere on the board
NRST: C33.1, R32.2, SW3.2, SWD1.10, U1.33 (NRST)
unnamed: C6.1, U1.80 (VCAP)
unnamed: C7.1, U1.133 (VCAP)
unnamed: C8.1, U1.172 (VCAP)
unnamed: C46.1, R50.2, TP52.1, Y1.1
unnamed: D3.2 (A), RN1.1 (R1.1)
unnamed: D4.2 (A), RN1.2 (R2.1)
unnamed: D5.2 (A), RN1.3 (R3.1)
unnamed: D6.2 (A), RN1.4 (R4.1)
unnamed: J9.2, R70.1
unnamed: J9.3, R69.1
unnamed: J11.2, R74.1
unnamed: J11.3, R75.1
unnamed: JP1.1 (A), M1.2 (+), R9.1
unnamed: M1.4 (PWM), Q1.3 (D), R9.2
unnamed: RN2.8 (R1.2), U1.1 (PE2)
unnamed: RN2.7 (R2.2), U1.3 (PE4)
unnamed: RN2.6 (R3.2), U1.4 (PE5)
unnamed: RN2.5 (R4.2), U1.5 (PE6)
unnamed: RN3.8 (R1.2), U1.85 (PB12)
unnamed: RN3.7 (R2.2), U1.86 (PB13)
unnamed: RN3.6 (R3.2), U1.87 (PB14)
unnamed: RN3.5 (R4.2), U1.88 (PB15)
unnamed: R3.2, U1.167 (BOOT0)
unnamed: TP78.1, U1.144 (PD1)
unnamed: TP79.1, U1.145 (PD2)
unnamed: TP80.1, U1.146 (PD3)
unnamed: C47.1, U1.31 (PH0), Y1.3
unnamed: R50.1, U1.32 (PH1)
unnamed: R46.2, U1.121 (VDD33USB)
unnamed: R47.2, U1.120 (VDD50USB)
unnamed: R48.2, R49.2, U1.16 (VDDSMPS)
SWCLK: R31.2, SWD1.4, U1.138 (PA14(JTCK)
SWDIO: R30.2, SWD1.2, U1.132 (PA13(JTMS)
U3_RX: R69.2, U1.90 (PD9)
U3_TX: R70.2, U1.89 (PD8)
U8_RX: R75.2, U1.102 (PJ9)
U8_TX: R74.2, U1.101 (PJ8)
VAA: C5.1, C61.1, U1.40 (VDDA), U11.1 (VDD), U11.3 (~SHDN); also elsewhere on the board
VDD: C1.1, C2.1, C3.1, C4.1, C49.1, C50.1, C51.1, C52.1, C53.1, C54.1, C55.1, C56.1, C57.1, C58.1, C59.1, C60.1, C63.1, C91.1, J4.9, J9.1, J10.2, J11.1, R8.1, R30.1, R31.1, R32.1, R46.1, R47.1, R48.1, R66.1, R67.1, R76.1, R77.1, SWD1.1, U1.7 (VDD), U1.8 (VBAT), U1.13 (VDD), U1.25 (VDD), U1.44 (VDD), U1.48 (VDD), U1.65 (VDD), U1.71 (VDD), U1.82 (VDDLDO), U1.84 (VDD), U1.92 (VDD), U1.99 (VDD), U1.105 (VDD), U1.113 (VDD), U1.126 (VDD), U1.135 (VDDLDO), U1.136 (VDD), U1.152 (VDD), U1.160 (VDD), U1.174 (PDR_ON), U1.175 (VDDLDO), U1.176 (VDD), U3.8 (VCC), U12.8 (V+); also elsewhere on the board
VREF: C62.1, U1.39 (VREF+), U11.7 (OUT), U11.8 (FB)

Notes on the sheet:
ADC1+ADC2
24MHz nominal
ADC2
EEPROM (STM32 Soft I2C)
22R
STM32 UART3
1kR
I2C grove (STM32 I2C4)
Button, LEDs
PCB Cooling Fan
STM32 UART8
SWD
ADC1+ADC2+ADC3
SPI bus LCD (STM32 SPI1)
PCB temp Ch2 (STM32 Soft I2C)
4-pin PC fan
